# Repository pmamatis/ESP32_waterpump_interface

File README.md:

# ESP32_waterpump_interface
A small project for an ESP32-doit-devKi-V1 to expose 4 GPIOs to BJTs in order to switch an external 5V powerlane driven by USB-C

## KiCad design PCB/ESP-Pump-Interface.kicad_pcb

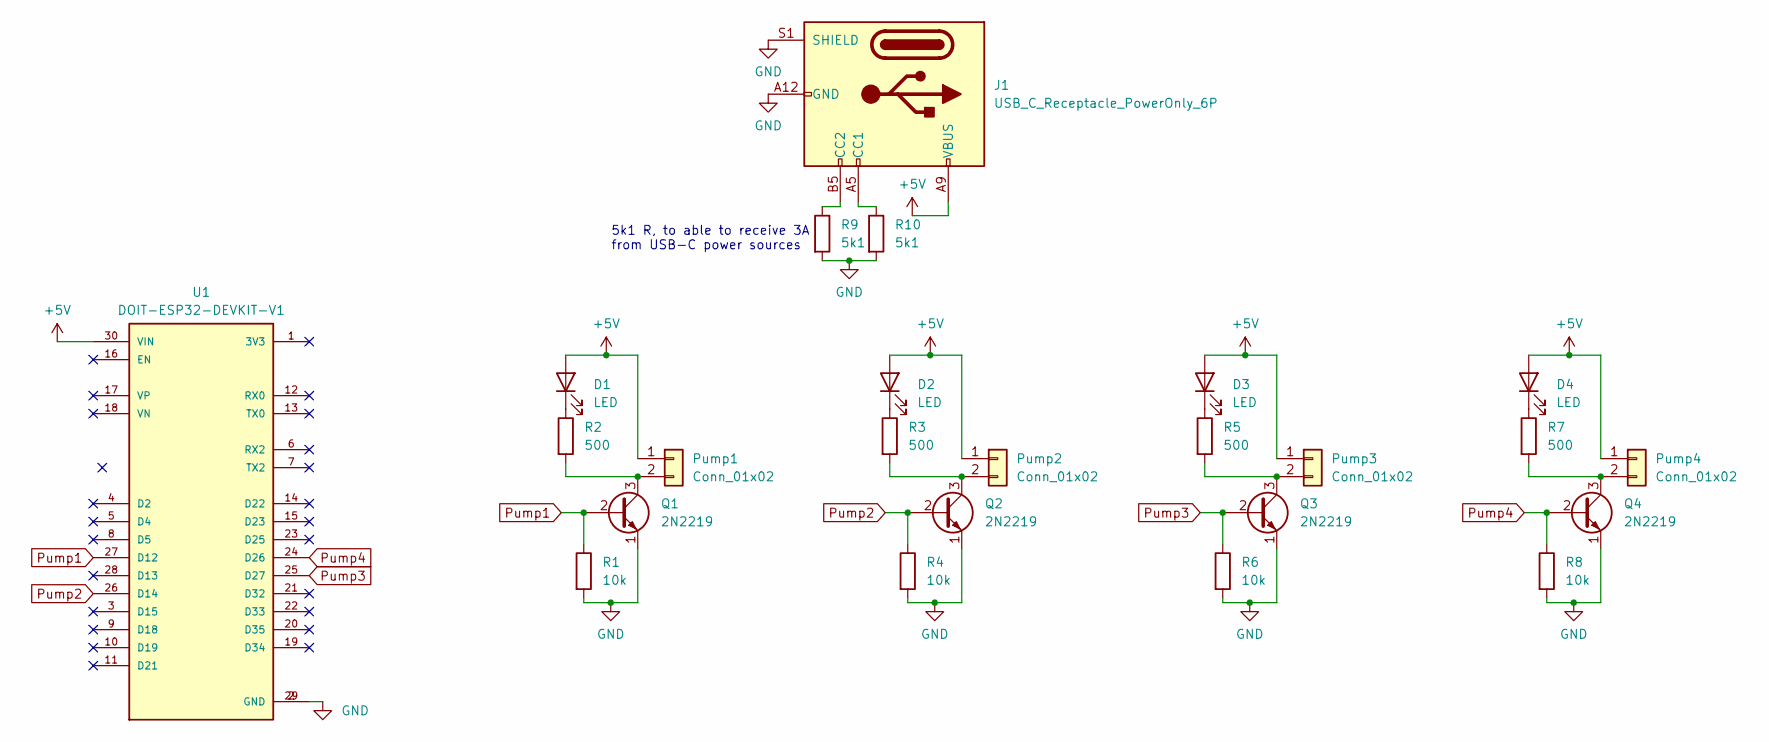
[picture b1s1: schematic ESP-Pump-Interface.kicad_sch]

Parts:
D1, D2, D3, D4: LED; LED_D5.0mm
J1: USB_C_Receptacle_PowerOnly_6P; USB_C_Receptacle_G-Switch_GT-USB-7010ASV
Pump1, Pump2, Pump3, Pump4: Conn_01x02; PinHeader_1x02_P2.54mm_Vertical
Q1, Q2, Q3, Q4: 2N2219; TO-92_Inline_Wide
R1, R4, R6, R8: 10k; R_Axial_DIN0204_L3.6mm_D1.6mm_P5.08mm_Horizontal
R2, R3, R5, R7: 500; R_Axial_DIN0204_L3.6mm_D1.6mm_P5.08mm_Horizontal
R9, R10: 5k1; R_Axial_DIN0204_L3.6mm_D1.6mm_P5.08mm_Horizontal
U1: DOIT-ESP32-DEVKIT-V1; MODULE_ESP32_DEVKIT_V1; PARTREV N/A

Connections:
+5V: D1.2 (A), D2.2 (A), D3.2 (A), D4.2 (A), J1.A9 (VBUS), J1.B9 (VBUS), Pump1.1, Pump2.1, Pump3.1, Pump4.1, U1.30 (VIN)
GND: J1.A12 (GND), J1.B12 (GND), J1.S1 (SHIELD), Q1.1 (E), Q2.1 (E), Q3.1 (E), Q4.1 (E), R1.2, R4.2, R6.2, R8.2, R9.2, R10.2, U1.2 (GND), U1.29 (GND)
unnamed: D1.1 (K), R2.1
unnamed: D2.1 (K), R3.1
unnamed: D3.1 (K), R5.1
unnamed: D4.1 (K), R7.1
unnamed: J1.A5 (CC1), R10.1
unnamed: J1.B5 (CC2), R9.1
unnamed: Pump1.2, Q1.3 (C), R2.2
unnamed: Pump2.2, Q2.3 (C), R3.2
unnamed: Pump3.2, Q3.3 (C), R5.2
unnamed: Pump4.2, Q4.3 (C), R7.2
Pump1: Q1.2 (B), R1.1, U1.27 (D12)
Pump2: Q2.2 (B), R4.1, U1.26 (D14)
Pump3: Q3.2 (B), R6.1, U1.25 (D27)
Pump4: Q4.2 (B), R8.1, U1.24 (D26)

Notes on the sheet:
5k1 R, to able to receive 3A from USB-C power sources

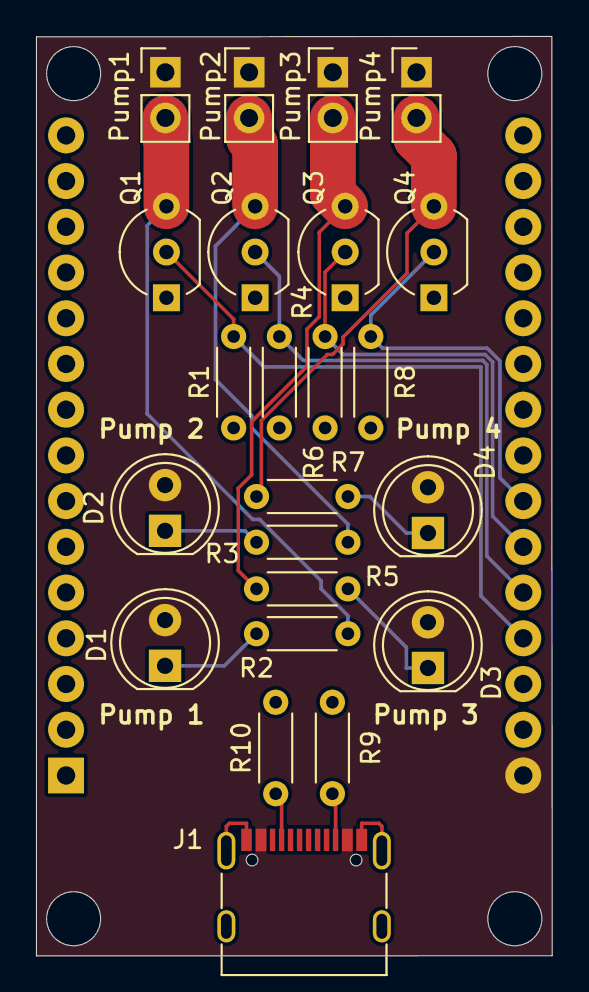
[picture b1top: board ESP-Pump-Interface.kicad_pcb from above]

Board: 2 copper layers, 28.7 x 51.1 mm, 24 parts (1 on the bottom side), 16 nets.

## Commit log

2024-06-13 added ESPHome yaml
2024-06-13 changed esp32-doit-devkit V1 symbol and footprint (source: SNAPEDA)
2024-06-13 esp32-doit-devkit-V1 symbol and footprint from SNAPEDA
2024-06-13 deleted backups
